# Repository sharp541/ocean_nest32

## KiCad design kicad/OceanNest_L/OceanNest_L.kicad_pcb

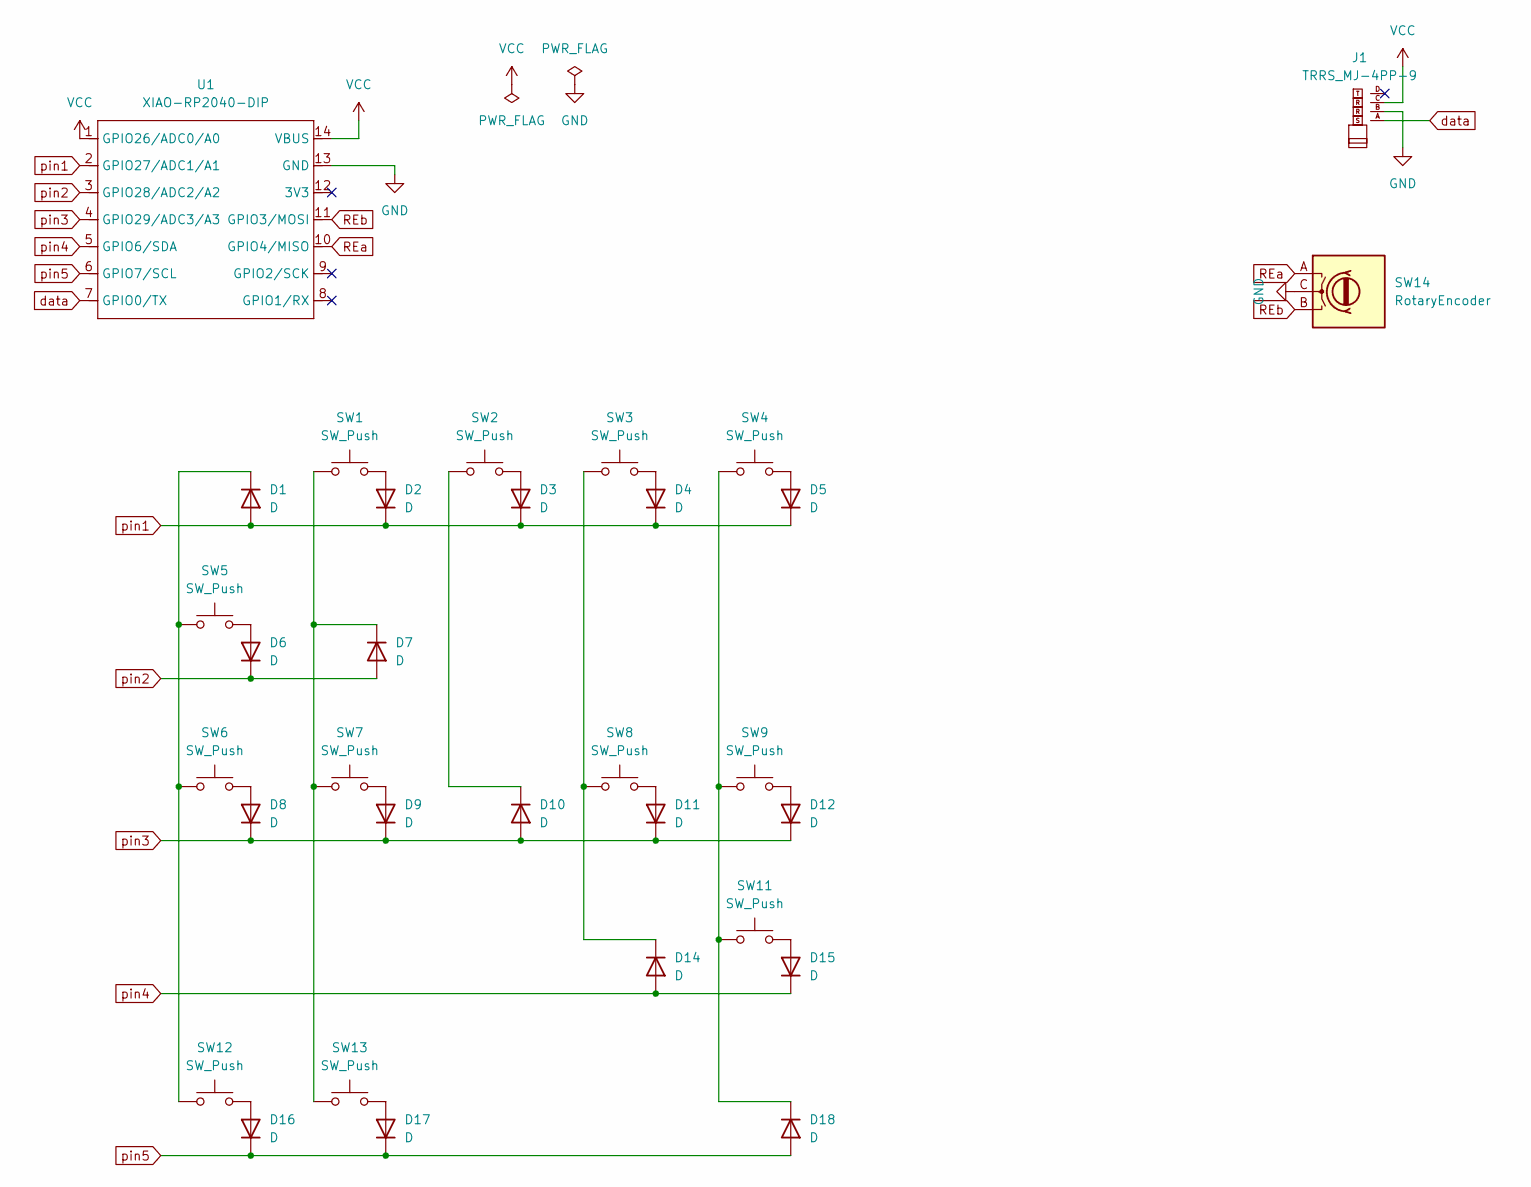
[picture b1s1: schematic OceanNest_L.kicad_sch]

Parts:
D1, D2, D3, D4, D5, D6, D7, D8, D9, D10, D11, D12, D14, D15, D16, D17, D18: D; Diode_SMD
J1: TRRS_MJ-4PP-9
SW1, SW2, SW3, SW4, SW5, SW6, SW7, SW8, SW9, SW11, SW12, SW13: SW_Push; CherryMX_Hotswap_16m
SW14: RotaryEncoder; RotaryEncoder_Alps_EC12E_Vertical_H20mm
U1: XIAO-RP2040-DIP; XIAO-RP2040-TH

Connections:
GND: J1.B, SW14.C, U1.13 (GND)
unnamed: D1.1 (K), SW5.1, SW6.1, SW12.1
unnamed: D2.2 (A), SW1.2
unnamed: D3.2 (A), SW2.2
unnamed: D4.2 (A), SW3.2
unnamed: D5.2 (A), SW4.2
unnamed: D6.2 (A), SW5.2
unnamed: D7.1 (K), SW1.1, SW7.1, SW13.1
unnamed: D8.2 (A), SW6.2
unnamed: D9.2 (A), SW7.2
unnamed: D10.1 (K), SW2.1
unnamed: D11.2 (A), SW8.2
unnamed: D12.2 (A), SW9.2
unnamed: D14.1 (K), SW3.1, SW8.1
unnamed: D15.2 (A), SW11.2
unnamed: D16.2 (A), SW12.2
unnamed: D17.2 (A), SW13.2
unnamed: D18.1 (K), SW4.1, SW9.1, SW11.1
REa: SW14.A, U1.10 (GPIO4/MISO)
REb: SW14.B, U1.11 (GPIO3/MOSI)
VCC: J1.C, U1.1 (GPIO26/ADC0/A0), U1.14 (VBUS)
data: J1.A, U1.7 (GPIO0/TX)
pin1: D1.2 (A), D2.1 (K), D3.1 (K), D4.1 (K), D5.1 (K), U1.2 (GPIO27/ADC1/A1)
pin2: D6.1 (K), D7.2 (A), U1.3 (GPIO28/ADC2/A2)
pin3: D8.1 (K), D9.1 (K), D10.2 (A), D11.1 (K), D12.1 (K), U1.4 (GPIO29/ADC3/A3)
pin4: D14.2 (A), D15.1 (K), U1.5 (GPIO6/SDA)
pin5: D16.1 (K), D17.1 (K), D18.2 (A), U1.6 (GPIO7/SCL)

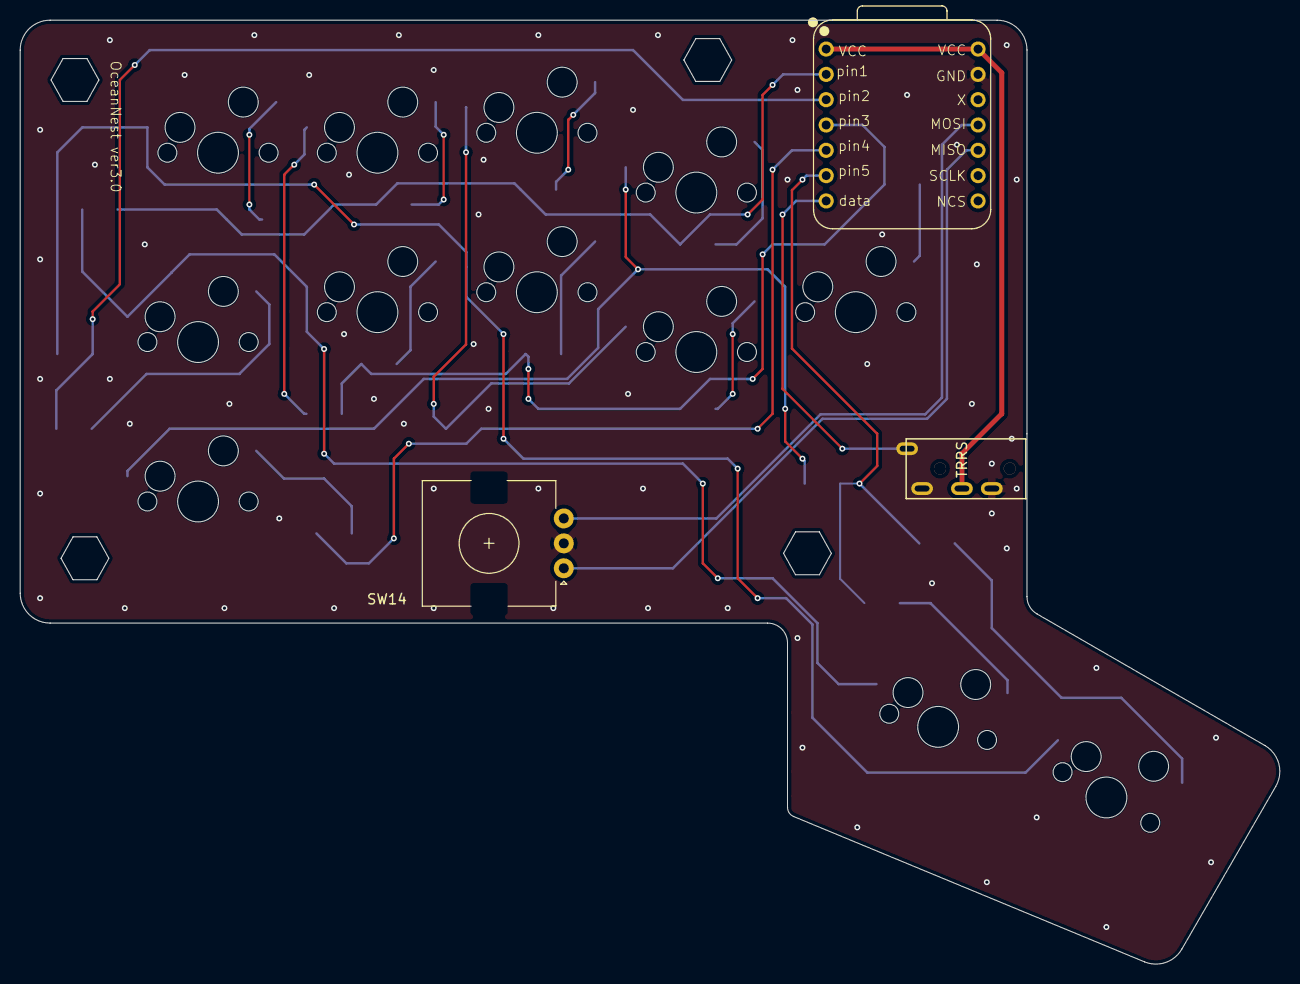
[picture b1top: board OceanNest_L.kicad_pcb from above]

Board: 2 copper layers, 126.4 x 94.7 mm, 38 parts (1 on the bottom side), 27 nets.

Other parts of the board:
hole1, hole2, hole2#2, hole2#3: Val**; m2_Spacer_Hole_hex
hole3, hole4: Val**; m2_Screw_Hole

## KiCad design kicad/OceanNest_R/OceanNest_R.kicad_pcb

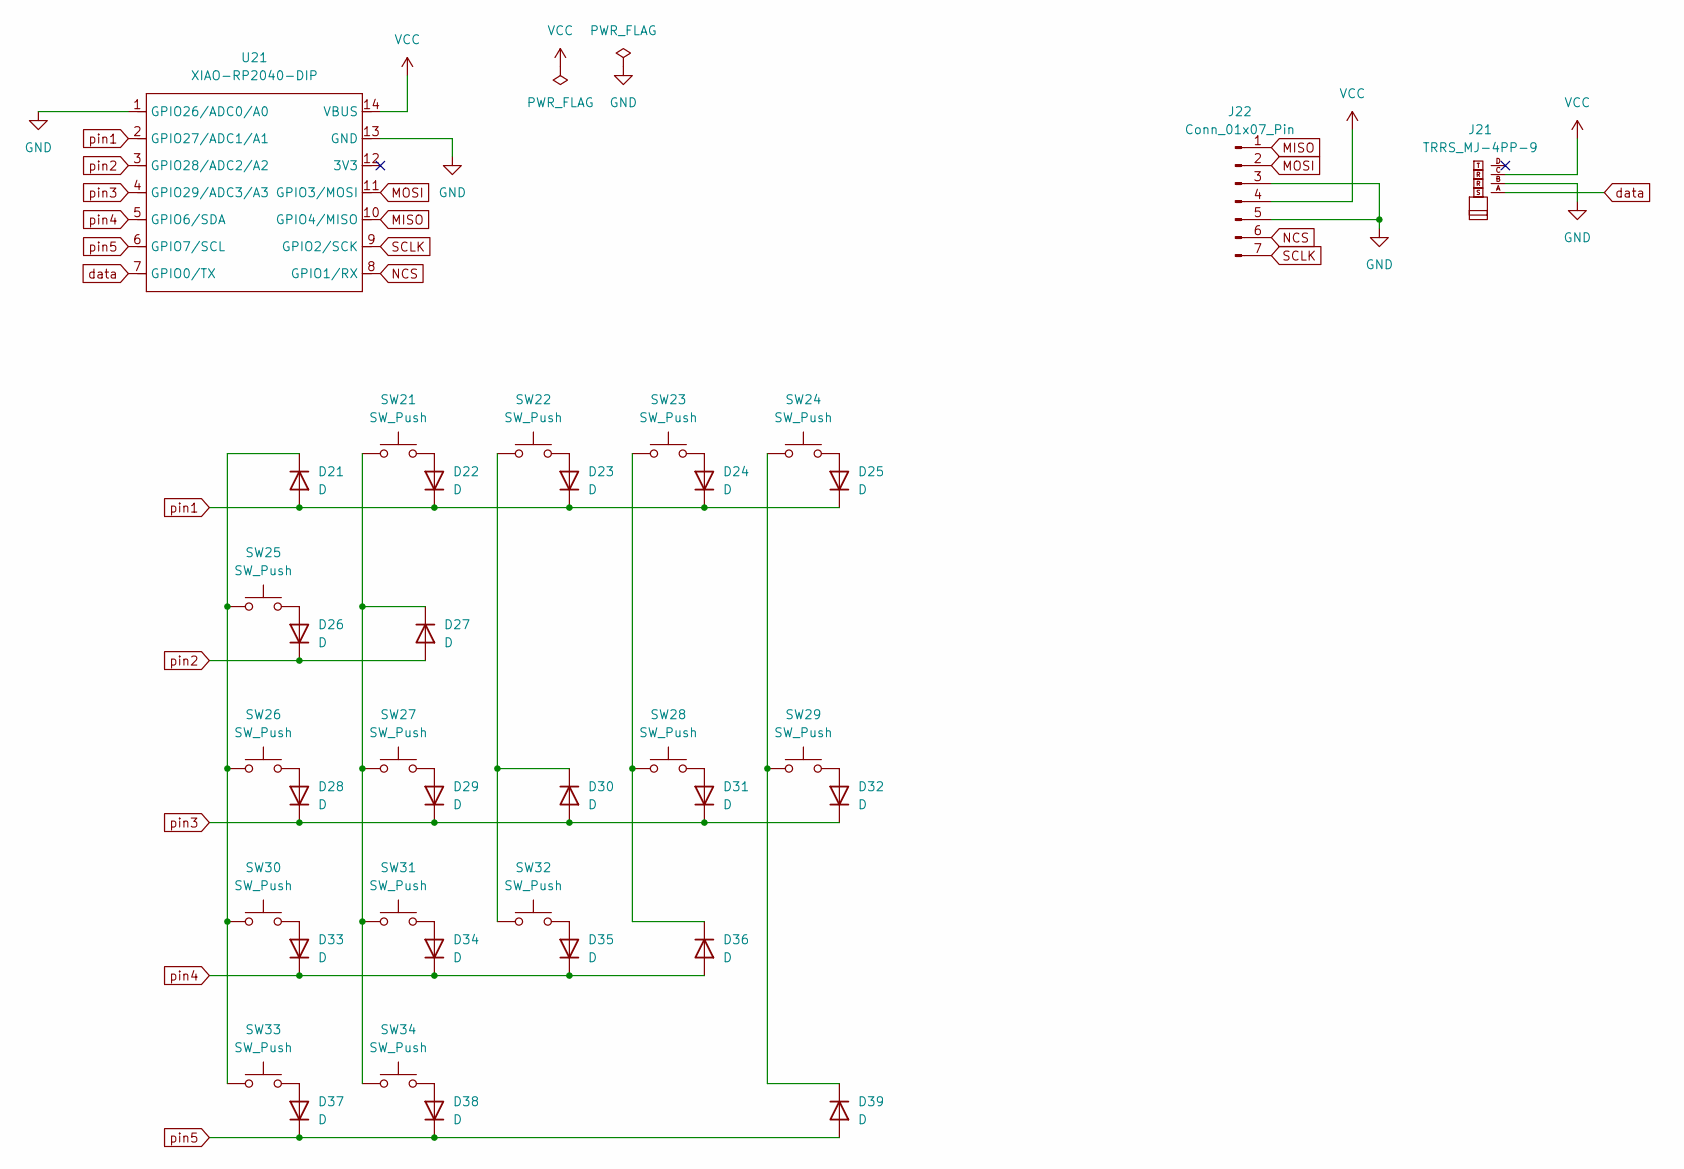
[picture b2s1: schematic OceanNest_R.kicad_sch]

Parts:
D21, D22, D23, D24, D25, D26, D27, D28, D29, D30, D31, D32, D33, D34, D35, D36, D37, D38, D39: D; Diode_SMD
J21: TRRS_MJ-4PP-9; MJ-4PP-9
J22: Conn_01x07_Pin; Mac8_L_7pin_contact_NEW2023
SW21, SW22, SW23, SW24, SW25, SW26, SW27, SW28, SW29, SW30, SW31, SW32, SW33, SW34: SW_Push; CherryMX_Hotswap_16m
U21: XIAO-RP2040-DIP

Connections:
GND: J21.B, J22.3, J22.5, U21.1 (GPIO26/ADC0/A0), U21.13 (GND)
MISO: J22.1, U21.10 (GPIO4/MISO)
MOSI: J22.2, U21.11 (GPIO3/MOSI)
NCS: J22.6, U21.8 (GPIO1/RX)
unnamed: D21.1 (K), SW25.1, SW26.1, SW30.1, SW33.1
unnamed: D22.2 (A), SW21.2
unnamed: D23.2 (A), SW22.2
unnamed: D24.2 (A), SW23.2
unnamed: D25.2 (A), SW24.2
unnamed: D26.2 (A), SW25.2
unnamed: D27.1 (K), SW21.1, SW27.1, SW31.1, SW34.1
unnamed: D28.2 (A), SW26.2
unnamed: D29.2 (A), SW27.2
unnamed: D30.1 (K), SW22.1, SW32.1
unnamed: D31.2 (A), SW28.2
unnamed: D32.2 (A), SW29.2
unnamed: D33.2 (A), SW30.2
unnamed: D34.2 (A), SW31.2
unnamed: D35.2 (A), SW32.2
unnamed: D36.1 (K), SW23.1, SW28.1
unnamed: D37.2 (A), SW33.2
unnamed: D38.2 (A), SW34.2
unnamed: D39.1 (K), SW24.1, SW29.1
SCLK: J22.7, U21.9 (GPIO2/SCK)
VCC: J21.C, J22.4, U21.14 (VBUS)
data: J21.A, U21.7 (GPIO0/TX)
pin1: D21.2 (A), D22.1 (K), D23.1 (K), D24.1 (K), D25.1 (K), U21.2 (GPIO27/ADC1/A1)
pin2: D26.1 (K), D27.2 (A), U21.3 (GPIO28/ADC2/A2)
pin3: D28.1 (K), D29.1 (K), D30.2 (A), D31.1 (K), D32.1 (K), U21.4 (GPIO29/ADC3/A3)
pin4: D33.1 (K), D34.1 (K), D35.1 (K), D36.2 (A), U21.5 (GPIO6/SDA)
pin5: D37.1 (K), D38.1 (K), D39.2 (A), U21.6 (GPIO7/SCL)

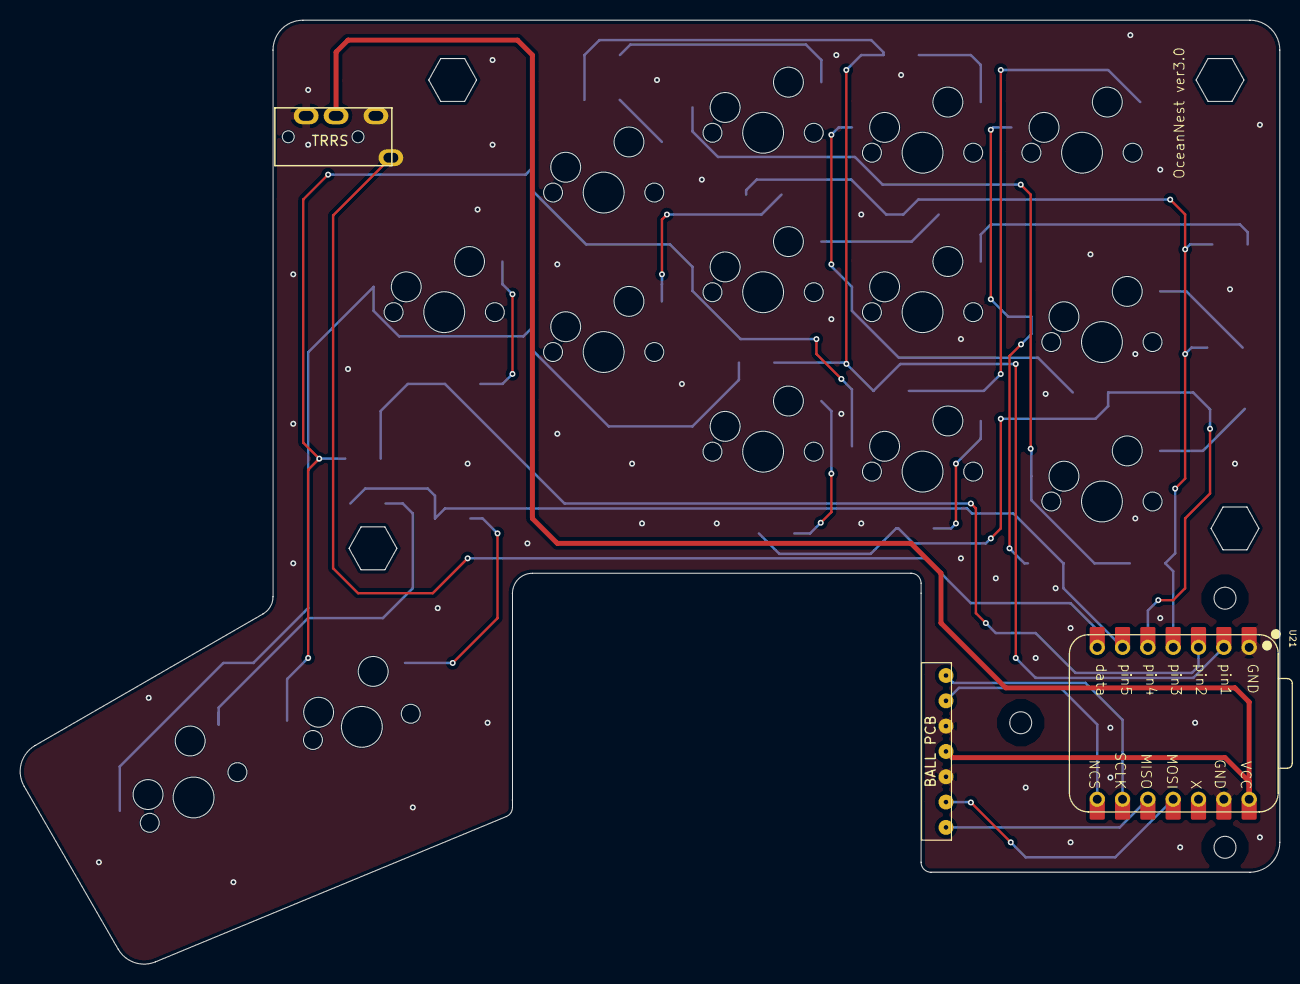
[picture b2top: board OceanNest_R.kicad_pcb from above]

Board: 2 copper layers, 126.4 x 94.7 mm, 43 parts (1 on the bottom side), 31 nets.

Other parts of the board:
hole1, hole1#2, hole2, hole2#2: Val**; m2_Spacer_Hole_hex
sc0, sc1, sc2: Val**; m2_Screw_Hole

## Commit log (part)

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2025-09-04 add initial keymap
2025-09-04 config: add SPI and pointing device configurations
2025-09-04 update: enhance SPI and pointing device support, add halconf and mcuconf configurations
2025-09-05 feat: add mouse layer support and dynamic keymap functionality
2025-09-06 fix PMW33XX_CS_PIN
2025-09-08 feat: implement scrolling mode for mouse layer and reorganize configuration files
2025-09-08 feat: add combo and tap dance functionality with configuration updates
2025-09-08 feat: expand dynamic keymap to support additional layers and update layer definitions
2025-09-08 feat: add KiCad PCB and schematic files for OceanNest project, including top and bottom layers
2025-09-09 feat: add DXF edge cuts file and update PCB properties for OceanNest project
2025-09-09 chore: update .gitignore to exclude backup files
2025-09-09 refactor: update PCB properties and footprints for OceanNest project, including footprint layer changes and model path adjustments
2025-09-09 chore: update .gitignore to include additional CAD file types and remove obsolete DXF edge cuts file
2025-09-13 feat: add new FreeCAD files and update PCB properties for OceanNest project, including layer selection and output format adjustments
2025-09-13 fix: update tapping term and combo term values in config.h for improved key response
2025-09-14 feat: enhance mouse control and keymap configuration with improved scrolling and key definitions
2025-09-14 fix: update keymap for mouse layer to improve functionality with new key definitions and shortcuts
2025-09-14 feat: implement custom key handling and auto-shift functionality with new key definitions and processing logic
2025-09-16 feat: update keymap layout for improved functionality and additional key definitions
2025-09-17 feat: add custom key handling to keymap for enhanced functionality
2025-09-18 feat: update alt combo key definitions and remove tap dance functionality
2025-09-18 feat: refactor custom key handling to use custom_key_t type for improved clarity and consistency
2025-09-18 feat: add custom key handling, auto-shift, and mouse control features with updated keymap structure
2025-09-18 feat: replace process_record.h with states.h for language state management
2025-09-19 feat: update alt combo key definition and adjust keymap layout for improved functionality
2025-09-22 feat: update esc combo key definition for improved keymap functionality
2025-10-03 feat: add mouse button functionality to keymap for enhanced control
2025-10-11 feat: refine keymap layout by adjusting mouse layer key definitions for improved functionality
2025-10-16 feat: update mouse layer key definitions for improved layout consistency
2025-11-24 feat: update PCB and schematic files for OceanNest project, including new components and layout adjustments
2025-11-24 feat: add new PCB and schematic files for OceanNest_L and OceanNest_L_Bottom, including layout adjustments and component updates
2025-11-25 feat: update hardware configuration and keymap layout.
2025-11-25 feat: update keymap layout and matrix configuration for improved functionality and consistency
2025-11-25 feat: add rotary encoder configuration for enhanced input control
2025-11-26 feat: increase layer count and update layer definitions for improved functionality
2025-11-26 feat: update keymap layers and add encoder map for enhanced functionality
2025-12-01 feat: update keyboard configuration with new PID/VID and enable bootmagic for enhanced functionality
2025-12-02 feat: update keymap layers with new key assignments for improved functionality
2025-12-08 feat: modify keymap layers with new key assignments for better layout and functionality
2025-12-10 feat: refine keymap layers and custom key functions for improved functionality
2025-12-20 feat: update pointing device configuration to PMW3610 and adjust rotation settings for improved tracking
2025-12-20 fix: update filenames and step files in OceanNest project for consistency and clarity
2025-12-21 fix: update pointing device driver to PMW3360 and adjust rotation settings for improved tracking accuracy
2025-12-21 fix: update encoder resolution to improve rotary input responsiveness
2026-01-08 fix: adjust autoshift behavior and keymap configurations for improved functionality
2026-01-09 fix: update keymap configurations for improved functionality and mouse layer adjustments
2026-01-09 fix: correct key assignments in default keymap for improved functionality
2026-01-20 fix: update PID in keyboard.json and refine key assignments in default keymap for improved functionality
2026-01-21 fix: update combo definitions and key assignments for improved functionality
2026-01-22 fix: update bootmagic configuration and refine encoder mappings for improved functionality
2026-01-22 feat: add new OceanNest_L and OceanNest_R PCB and project files for enhanced design capabilities
2026-01-23 fix: adjust layer count, update combo definitions, and refine key assignments for improved functionality
2026-01-23 fix: refine key assignments in default keymap for improved functionality
2026-02-04 fix: update right parenthesis and brace combo definitions for consistency
2026-02-13 feat: implement PMW3610 pointing device driver and update configuration
2026-02-24 fix: update combo definitions and key assignments for consistency and improved functionality
2026-02-24 fix: update mouse layer key assignments for improved functionality
2026-02-24 fix: rename combo variables for consistency in keymap definitions
2026-03-09 fix: adjust tapping and combo timing for improved responsiveness
2026-03-09 fix: update left and right combo definitions for improved key mapping consistency
2026-03-09 fix: correct up arrow right combo definition for accurate key mapping
2026-04-09 chore: add local qmk build setup
2026-04-09 Add AZIK-style default keymap input state
2026-04-09 update keymap
2026-04-10 fix scroll sensitivity after qmk update
2026-04-10 update combo
2026-04-10 Add keymap SVG generation workflow
2026-04-10 Update keymap drawer AZIK legends
2026-04-11 Update AZIK ui/ao mappings
2026-04-16 Update AZIK combos and keymap for improved functionality
2026-04-16 Update keymap drawer for revised layout
2026-04-19 Fix W keymap drawer legend
2026-04-22 Update AZIK combos and keymap for enhanced functionality
2026-04-22 Update keymap drawer layout data
2026-04-22 Add QMK .build symlink in init
2026-05-25 change layout
2026-05-26 Update keymap drawer layout
